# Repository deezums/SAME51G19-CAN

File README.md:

# SAME51G19-CAN
Atmel ATSAME51G19A breakout board with TI TCAN33x transciever

.. image:: https://github.com/deezums/SAME51G19-CAN/raw/master/extras/photos/SAME51G19A_CAN_INDEX.jpg 

This is version 1.0 of my ATSAME51G19A breakout board. 

Includes a 3.3V LDO, usb power, a led on PB22, reset switch, and 3V power led.

The canbus transiever contains a common mode choke, tvs array, and plenty of filter caps which can be optimally tuned to bus frequency. 

Digital split bus termiation using a mosfet array and resistors matched to rds, solder jumper allows disable, permanant pullup, or CPU control through PA21. 

Mostly 0402 components...

Tested working with atmel studio start examples and ATSAME54XPLAINED board. Hope to eventually port to Arduino with proper canbus library support.

Issues...

CMC pads should be narrowed vertically and can be horizontally compressed a fair bit.

Solder jumper pads are terrible, think too narrow and sharp. If not for 63/37 I don't think I could use them. 

TCAN33x, the extra function pins are not currently routed to CPU pins. Use TCAN332, or route the extra pins if you want to use hardware features of other variants.

Why did I make the silkscreen so small?! What pin is this!!

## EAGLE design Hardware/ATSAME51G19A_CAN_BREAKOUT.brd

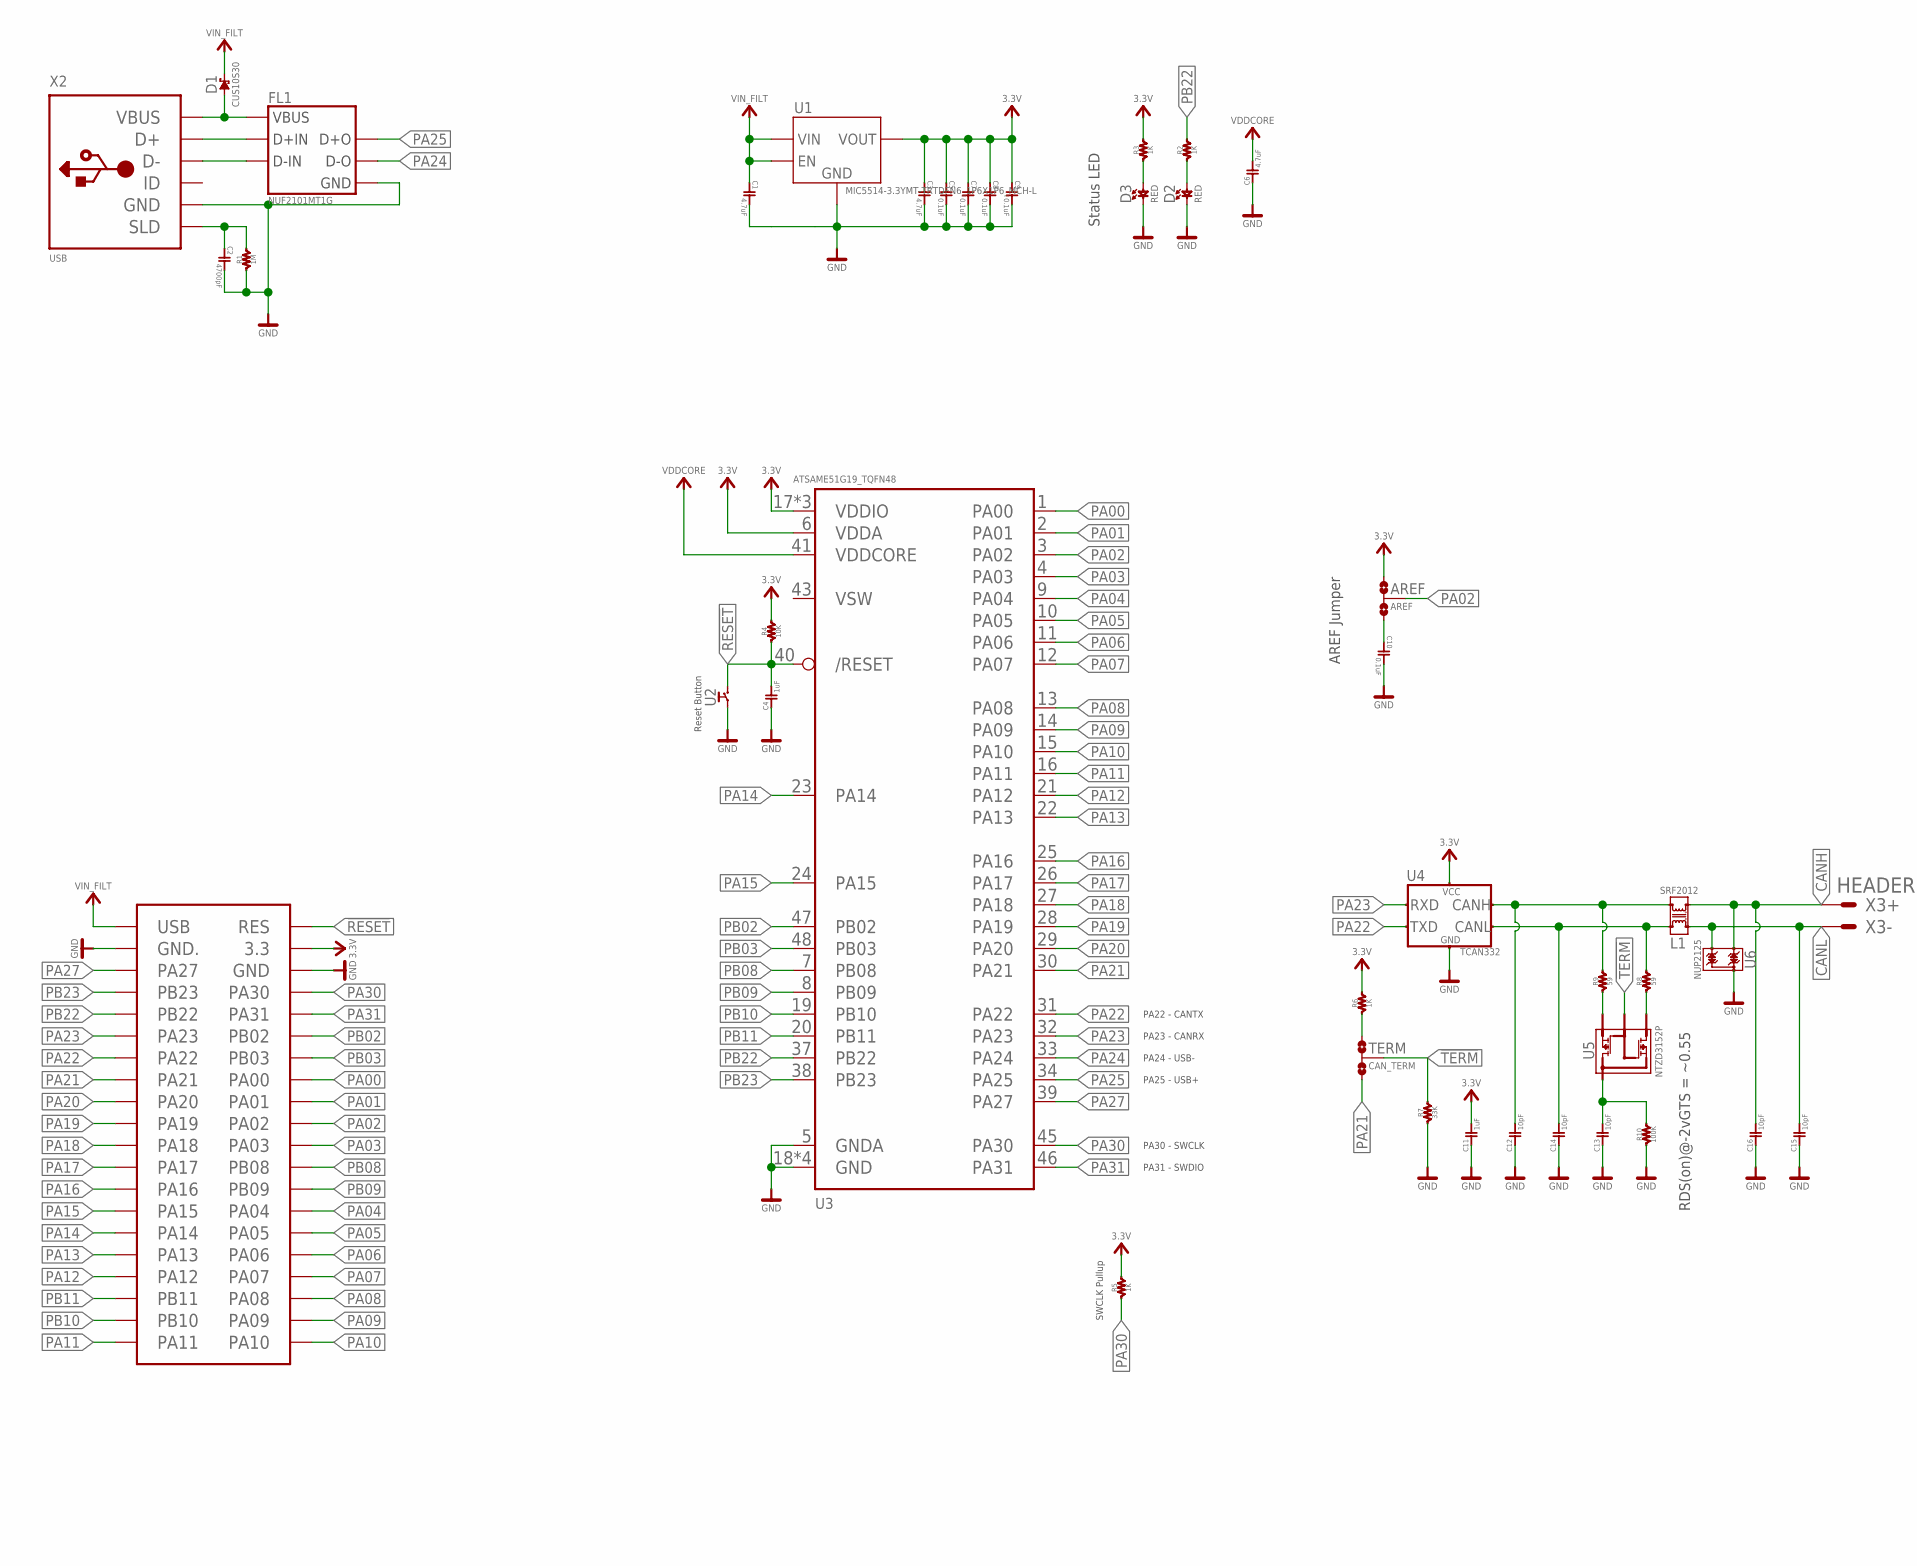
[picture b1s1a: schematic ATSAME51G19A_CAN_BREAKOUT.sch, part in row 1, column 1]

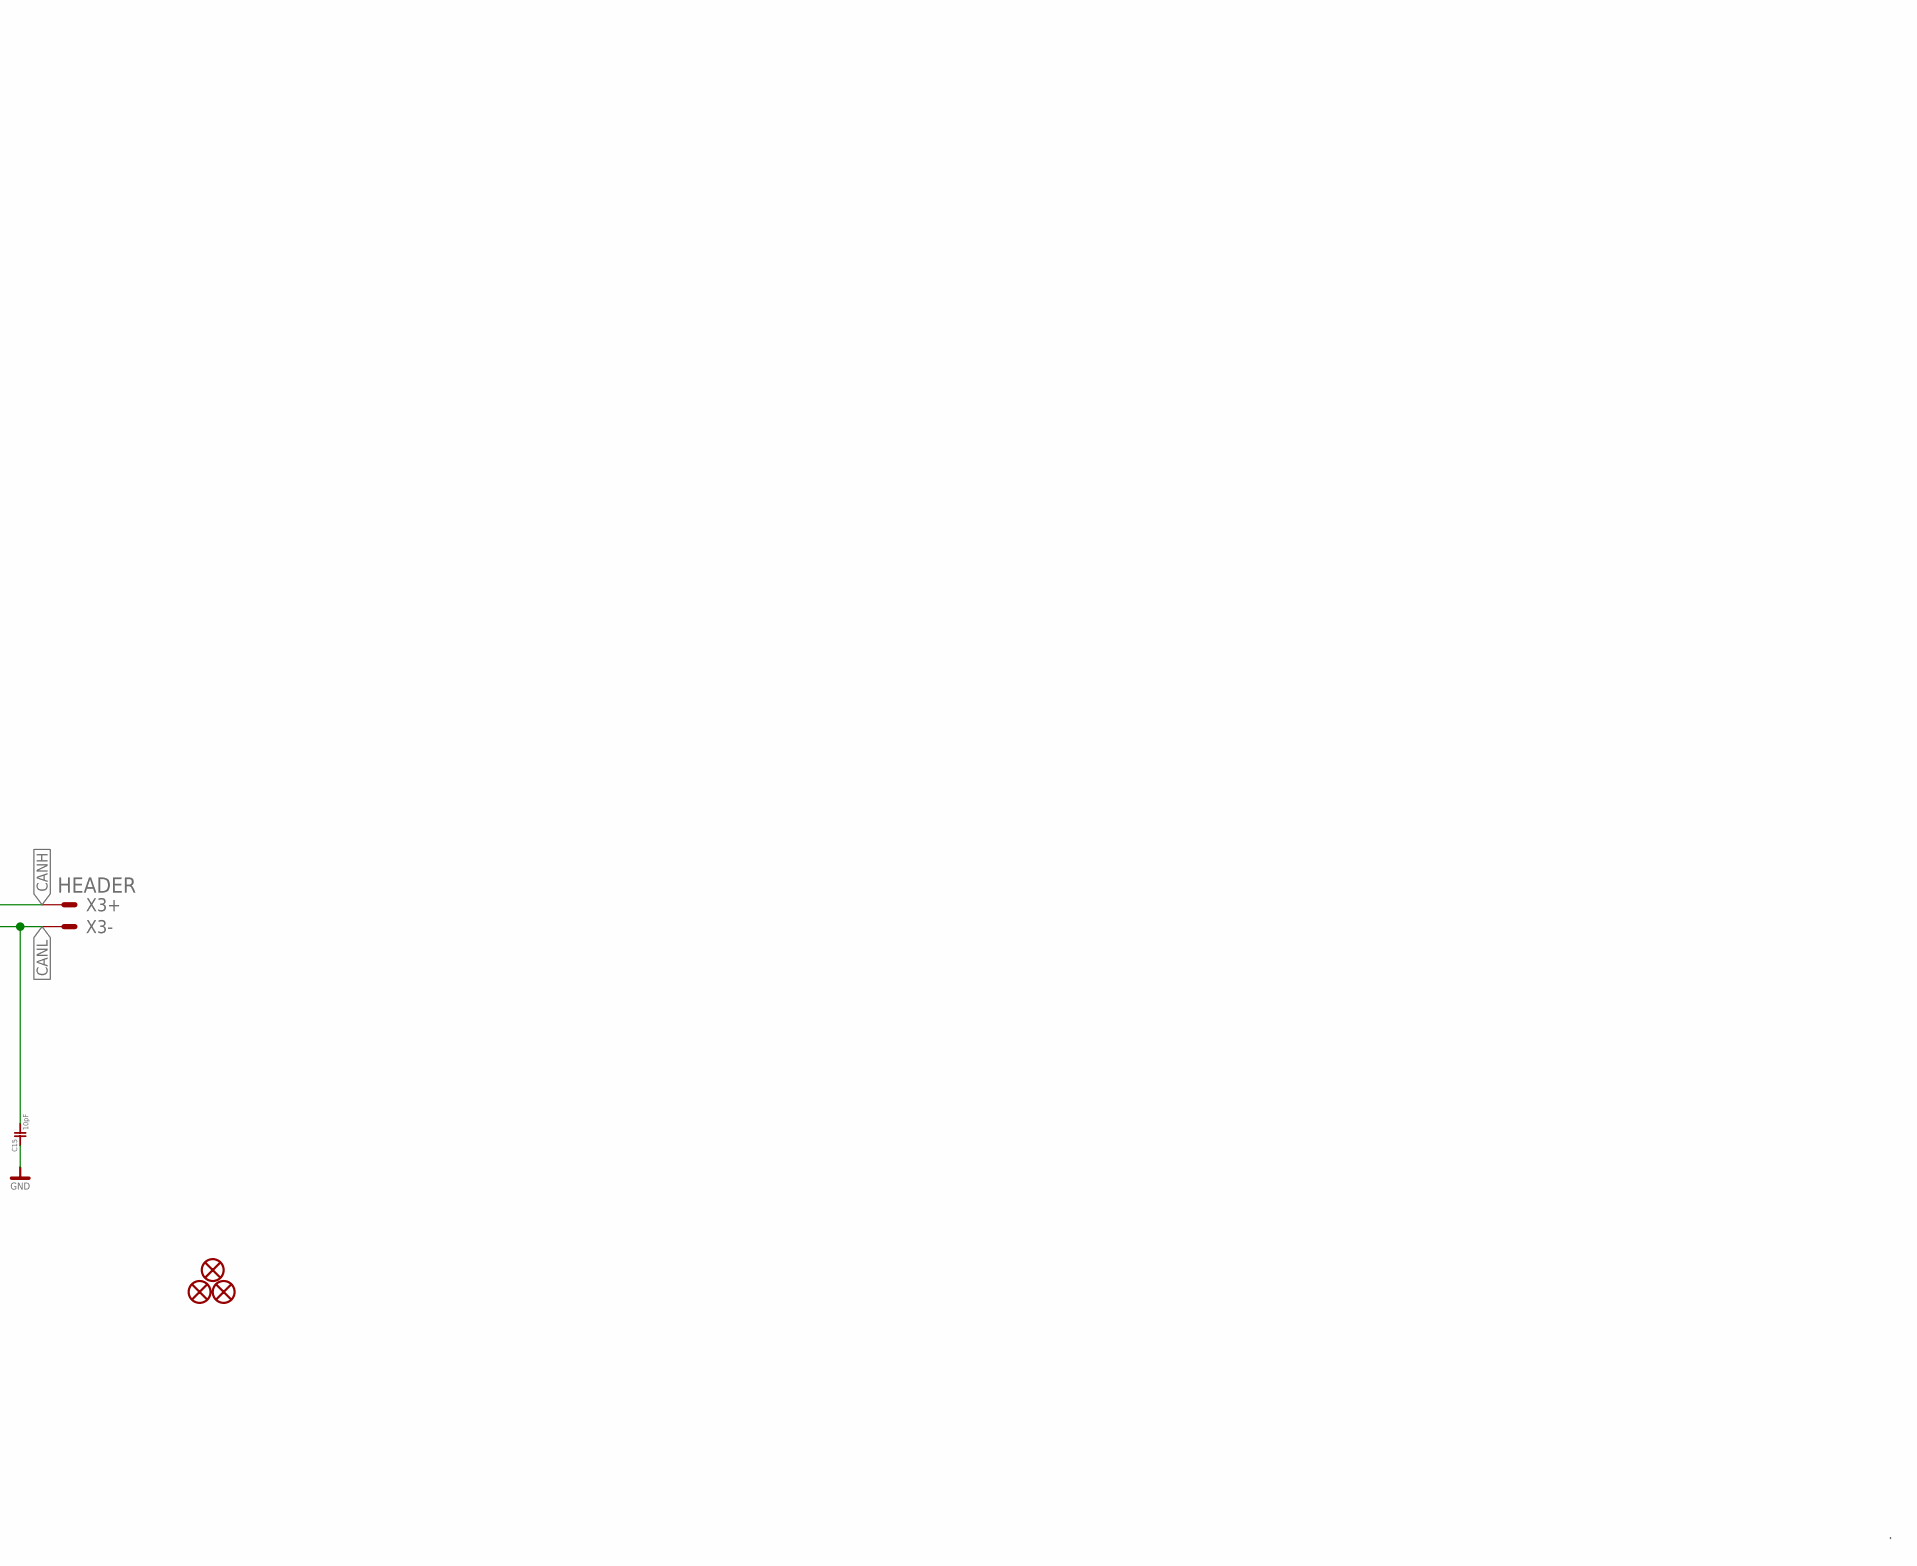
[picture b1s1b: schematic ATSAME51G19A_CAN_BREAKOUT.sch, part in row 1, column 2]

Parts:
AREF: AREF; C0R-JMP
C1: 4.7uF; CAP0402; VOLTAGE 10V; MPN CL05A106MP8NUB8
C2: 4700pF; CAP0402; VOLTAGE 25V; MPN CC0402KRX7R8BB472
C3, C6: 4.7uF; CAP0402; VOLTAGE 6.3V; MPN GRM155R60J106ME05D
C4, C11: 1uF; CAP0402; VOLTAGE 6.3V; MPN CL05A105KQ5NNNC
C5, C7, C8, C9, C10: 0.1uF; CAP0402; VOLTAGE 6.3V; MPN CL05A105KQ5NNNC
C12, C13, C14, C15, C16: 10pF; CAP0402; VOLTAGE 50V; MPN C0402C100K5RAC7867
D1: CUS10S30; X3-WLB1608-2; MPN SDM2U30CSP-7
D2, D3: 0603 LED; LED-0603; MPN LNJ8W0C83RA
FID1, FID2, FID3: MICROBUILDER_FIDUCIAL_0.5MM
FL1: NUF2101MT1G; SOT95P275X110-6N
L1: SRF2012; SRF2012AA; MPN SRF2012-121YA
R1: 1M; RES0402; TOLERANCE 1%; MPN PFR05S-105-FNH
R2, R3: 1K; RES0402; TOLERANCE 1%; MPN CR0402-FX-1002GLF
R4: 10K; RES0402; TOLERANCE 1%; MPN CR0402-FX-1002GLF
R5, R6: 1K; RES0402; TOLERANCE 1%; MPN PFR05S-102-FNH
R7: 33K; RES0402; TOLERANCE 1%; MPN RMCF0402FT33K0
R8, R9: 59; RES0603; TOLERANCE 1%; MPN CRCW060359R0FKEAHP
R10: 100K; RES0402; TOLERANCE 1%; MPN CR0402-FX-1003GLF
TERM: CAN_TERM; C0R-JMP
U1: MIC5514-3.3YMT-TRTDFN6_1P6X1P6_MCH-L; TDFN6_1P6X1P6_MCH-L
U2: PUSH_SWITCHPTS815; SWITCH_PTS815; MPN PTS815 SJM 250 SMTR LFS
U3: ATSAME51G19_TQFN48; TQFN48_7MM; MPN ATSAME51G19A-MF
U4: TCAN332; DCN0008A; MPN TCAN332DCNR
U5: NTZD3152P; SOT-563; MPN NTZD3152PT1G
U6: NUP2125; SC70; MPN NUP2125WTT1G
X1: CONN; BOARDOUTLINE
X2: USB; 10118194
X3: HEADER; 22-23-2021

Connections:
3.3V: AREF.1, C3.1 (C1), C5.1 (C1), C7.1 (C1), C8.1 (C1), C9.1 (C1), C11.2 (C2), R3.2, R4.2, R5.2, R6.2, U1.4 (VOUT), U1.5 (VOUT), U3.6 (VDDA), U3.17 (VDDIO), U3.36 (VDDIO), U3.44 (VDDIO), U4.3 (VCC), X1.3.3
!RESET: C4.2 (C2), R4.1, U2.P$3 (2), U2.P$4 (2), U3.40 (/RESET), X1.!RES (RES)
!TERM: R7.2, TERM.2, U5.P$2 (GATE), U5.P$5 (GATE)
CANH: C16.2 (C2), L1.4, U6.1, X3.1
CANL: C15.2 (C2), L1.1, U6.2, X3.2
GND: C1.2 (C2), C2.2 (C2), C3.2 (C2), C4.1 (C1), C5.2 (C2), C6.1 (C1), C7.2 (C2), C8.2 (C2), C9.2 (C2), C10.2 (C2), C11.1 (C1), C12.1 (C1), C13.1 (C1), C14.1 (C1), C15.1 (C1), C16.1 (C1), D2.C, D3.C, FL1.2 (GND), R1.1, R7.1, R10.1, U1.6 (GND), U1.7 (GND), U2.P$1 (1), U2.P$2 (1), U3.5 (GNDA), U3.18 (GND), U3.35 (GND), U3.42 (GND), U3.THERMAL (GND), U4.2 (GND), U6.3, X1.GND, X1.GND., X2.5 (GND)
unnamed: C13.2 (C2), R10.2, U5.P$4 (DRAIN1), U5.P$6 (DRAIN1)
unnamed: R8.1, U5.P$3 (DRAIN2)
unnamed: D3.A, R3.1
unnamed: FL1.6 (D+I), X2.3 (D+)
unnamed: D2.A, R2.1
unnamed: FL1.4 (D-_I), X2.2 (D-)
unnamed: R6.1, TERM.1
unnamed: C2.1 (C1), R1.2, X2.GND4 (SLD), X2.GND5 (SLD), X2.P$1 (SLD), X2.P$2 (SLD), X2.P$3 (SLD), X2.P$4 (SLD)
unnamed: AREF.3, C10.1 (C1)
unnamed: C14.2 (C2), L1.2, R8.2, U4.6 (CANL)
unnamed: R9.1, U5.P$1 (SOURCE1)
unnamed: C12.2 (C2), L1.3, R9.2, U4.7 (CANH)
PA00: U3.1 (PA00), X1.PA00
PA01: U3.2 (PA01), X1.PA01
PA02: AREF.2, U3.3 (PA02), X1.PA02
PA03: U3.4 (PA03), X1.PA03
PA04: U3.9 (PA04), X1.PA04
PA05: U3.10 (PA05), X1.PA05
PA06: U3.11 (PA06), X1.PA06
PA07: U3.12 (PA07), X1.PA07
PA08: U3.13 (PA08), X1.PA08
PA09: U3.14 (PA09), X1.PA09
PA10: U3.15 (PA10), X1.PA10
PA11: U3.16 (PA11), X1.PA11
PA12: U3.21 (PA12), X1.PA12
PA13: U3.22 (PA13), X1.PA13
PA14: U3.23 (PA14), X1.PA14
PA15: U3.24 (PA15), X1.PA15
PA16: U3.25 (PA16), X1.PA16
PA17: U3.26 (PA17), X1.PA17
PA18: U3.27 (PA18), X1.PA18
PA19: U3.28 (PA19), X1.PA19
PA20: U3.29 (PA20), X1.PA20
PA21: TERM.3, U3.30 (PA21), X1.PA21
PA22: U3.31 (PA22), U4.1 (TXD), X1.PA22
PA23: U3.32 (PA23), U4.4 (RXD), X1.PA23
PA24: FL1.3 (D-_O), U3.33 (PA24)
PA25: FL1.1 (D+_O), U3.34 (PA25)
PA27: U3.39 (PA27), X1.PA27
PA30: R5.1, U3.45 (PA30), X1.PA30
PA31: U3.46 (PA31), X1.PA31
PB02: U3.47 (PB02), X1.PB02
PB03: U3.48 (PB03), X1.PB03
PB08: U3.7 (PB08), X1.PB08
PB09: U3.8 (PB09), X1.PB09
PB10: U3.19 (PB10), X1.PB10
PB11: U3.20 (PB11), X1.PB11
PB22: R2.2, U3.37 (PB22), X1.PB22
PB23: U3.38 (PB23), X1.PB23
VBUS: D1.ANNODE, FL1.5 (VBUS), X2.1 (VBUS)
VDDCORE: C6.2 (C2), U3.41 (VDDCORE)
VIN_FILT: C1.1 (C1), D1.CATHODE, U1.1 (EN), U1.2 (EN), U1.3 (VIN), X1.USB

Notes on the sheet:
PA25 - USB+
PA24 - USB-
PA23 - CANRX
PA22 - CANTX
PA30 - SWCLK
PA31 - SWDIO
Reset Button
SWCLK Pullup
AREF Jumper
Status LED
RDS(on)@-2vGTS = ~0.55

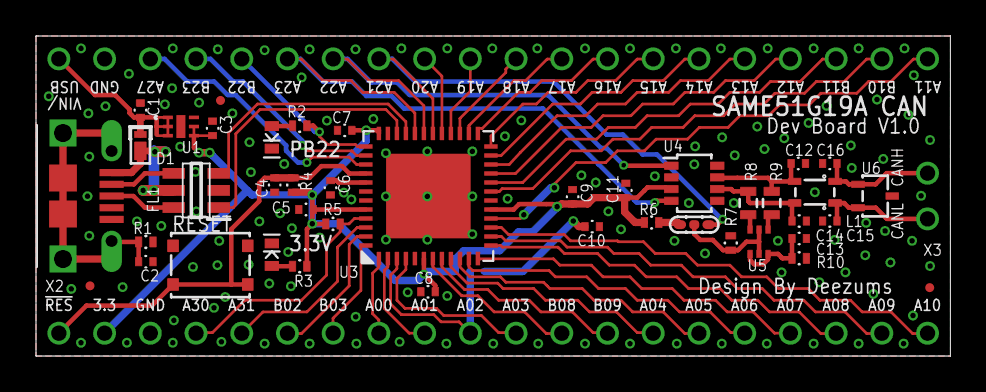
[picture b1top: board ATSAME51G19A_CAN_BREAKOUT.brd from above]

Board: 2 copper layers, 50.8 x 17.8 mm, 45 parts (1 on the bottom side), 58 nets.

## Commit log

2020-09-16 Init

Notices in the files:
parts and their libraries:
COPYRIGHT: Copyright (C) 2018 Accelerated Designs. All rights reserved
